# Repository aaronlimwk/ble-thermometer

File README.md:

# BLE Contactless Thermometer 🤒
A BLE contactless thermometer which can distinguish between colds and the flu!

## Front & Back View 🌡️

## Features ⚙️

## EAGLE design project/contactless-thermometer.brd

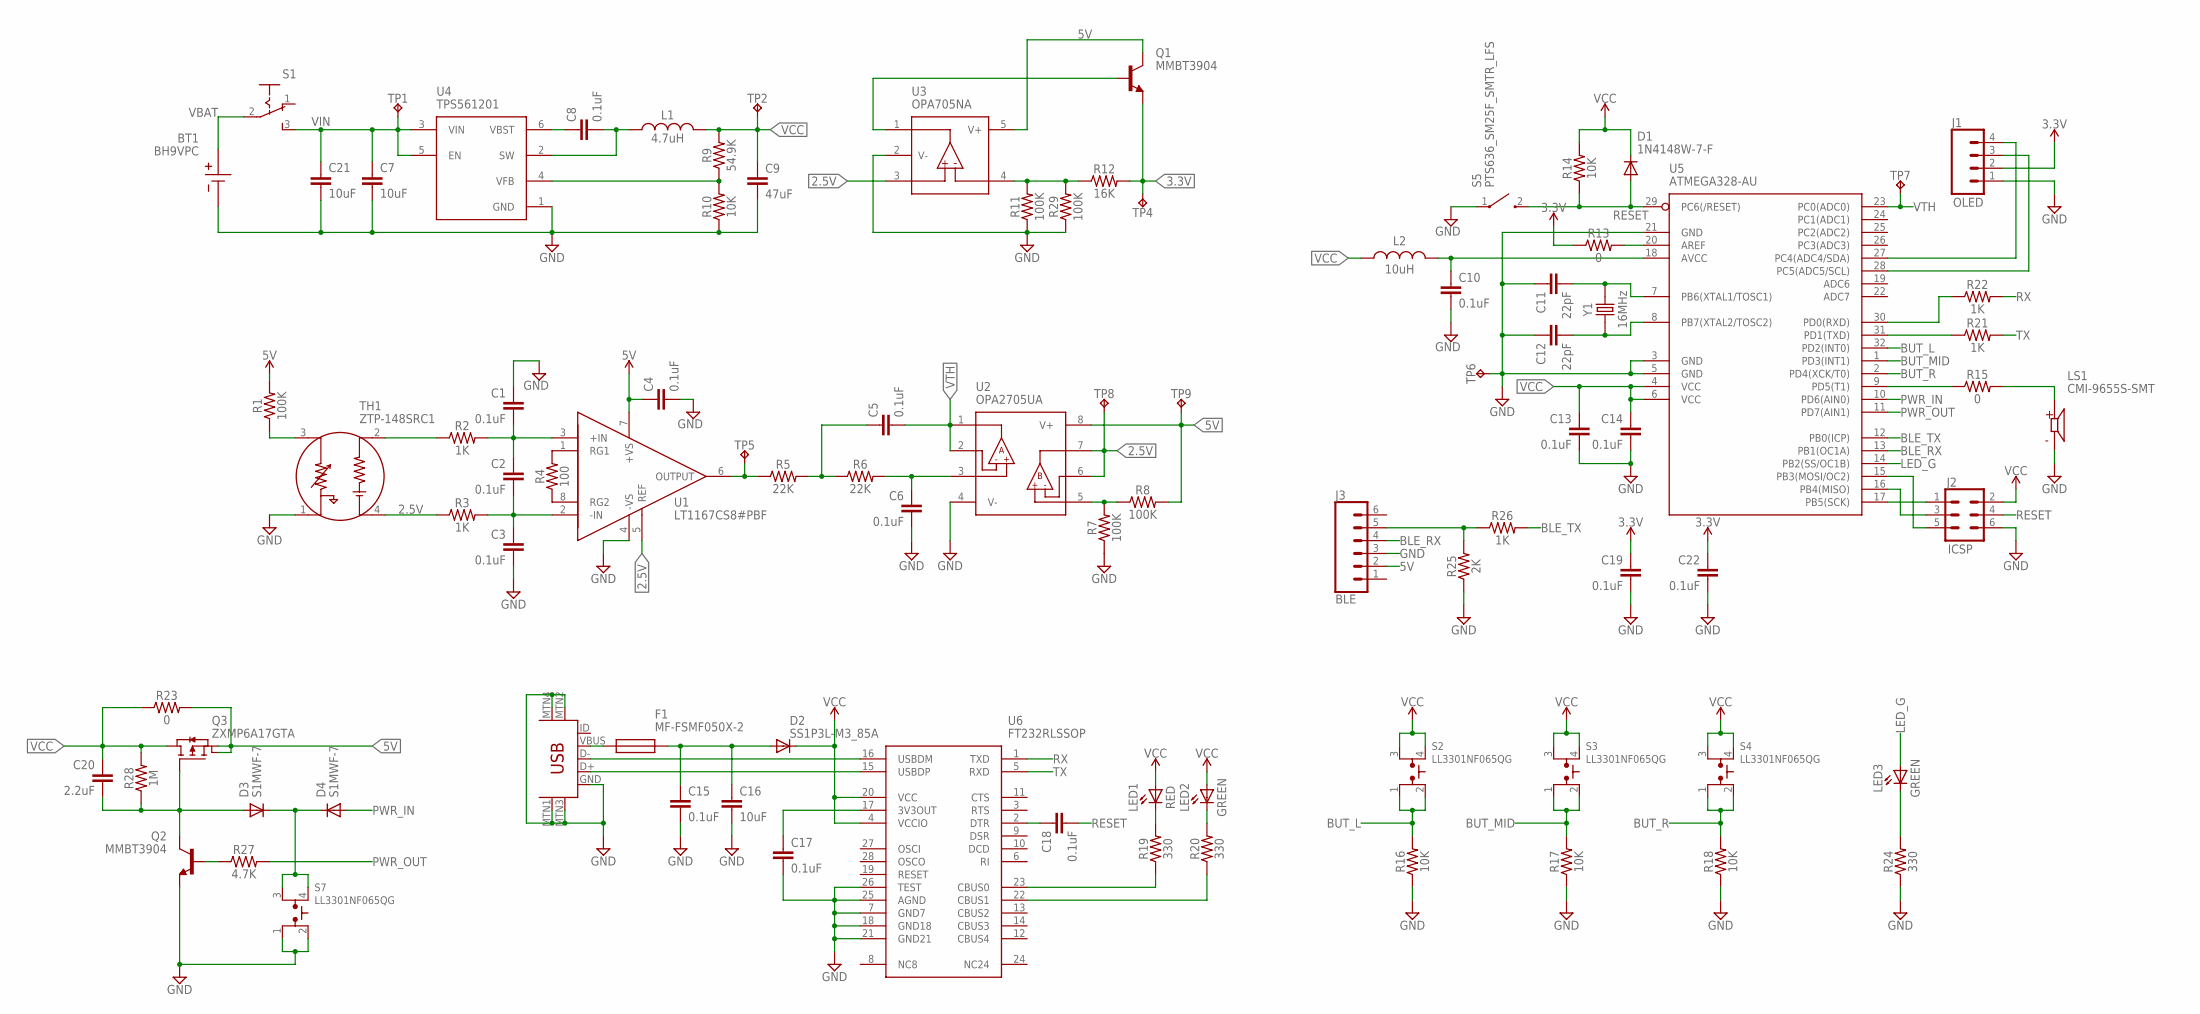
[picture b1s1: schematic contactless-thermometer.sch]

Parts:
BT1: BH9VPC; BAT_BH9VPC
C1, C2, C3, C4, C5, C6, C8, C10, C13, C14, C15, C17, C18, C19, C22: 0.1uF; 0603
C7, C21: 10uF; CAPC2012X145N
C9: 47uF; 1206
C11, C12: 22pF; 0603
C16: 10uF; 1206
C20: 2.2uF; CAPC2012X145N
D1: 1N4148W-7-F; SOD3716X145N
D2: SS1P3L-M3_85A; SMP
D3, D4: S1MWF-7; SODFL3518X115N
F1: MF-FSMF050X-2; FUSC1608X100N
J1: OLED; 1X04
J2: ICSP; 2X3
J3: BLE; 1X06
J4: USB-MINIB-5PIN; USB-MINIB
L1: 4.7uH; VLCF5020T4R7N1R71
L2: 10uH; INDC2012X145N
LED1: RED; AA1608CGSK
LED2, LED3: GREEN; AA1608CGSK
LS1: CMI-9655S-SMT; CUI_CMI-9655S-SMT
Q1, Q2: MMBT3904; SOT23_NXP
Q3: ZXMP6A17GTA; SOT230P700X180-4N
R1, R7, R8, R11, R29: 100K; 0603
R2, R3, R21, R22, R26: 1K; 0603
R4: 100; 0603
R5, R6: 22K; 0603
R9: 54.9K; 0603
R10, R14, R16, R17, R18: 10K; 0603
R12: 16K; 0603
R13, R15, R23: 0; 0603
R19, R20, R24: 330; 0603
R25: 2K; 0603
R27: 4.7K; 0603
R28: 1M; 0603
S1: SK12F17G7; SW3_2F17G7_CNK
S2, S3, S4, S7: LL3301NF065QG
S5: PTS636_SM25F_SMTR_LFS; PTS636SM25FSMTRLFS
TH1: ZTP-148SRC1; XDCR_ZTP-148SRC1
TP1, TP2, TP4, TP5, TP6, TP7, TP8, TP9: TPTP10R; TP10R
U1: LT1167CS8#PBF; SOIC127P599X175-8N
U2: OPA2705UA; SOIC127P600X175-8N
U3: OPA705NA; SOT95P280X145-5N
U4: TPS561201; SOT95P280X110-6N
U5: ATMEGA328-AU; TQFP32-08
U6: FT232RLSSOP; SOP65P780X200-28N
Y1: 16MHz; XTAL_ECS-240-20-5PX-TR

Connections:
2.5V: R3.1, TH1.4 (THERMOPILE_GND), TP8.TP, U1.5 (REF), U2.6 (-INB), U2.7 (OUTB), U3.3 (+IN)
3.3V: C19.1, C22.1, J1.2, Q1.2, R12.2, R13.1, TP4.TP
5V: C4.1, J3.2, Q1.3, Q3.2 (D1), Q3.4 (D2), R1.2, R8.2, R23.2, TP9.TP, U1.7 (+VS), U2.8 (V+), U3.5 (V+)
AVCC: C10.1, L2.2, U5.18 (AVCC)
BLE_TX: R26.2, U5.12 (PB0(ICP))
BUT_L: R16.2, S2.1, S2.2, U5.32 (PD2(INT0))
BUT_MID: R17.2, S3.1, S3.2, U5.1 (PD3(INT1))
BUT_R: R18.2, S4.1, S4.2, U5.2 (PD4(XCK/T0))
BUZZ: R15.1, U5.9 (PD5(T1))
DTR: C18.1, U6.2 (DTR)
GND: BT1.-, C1.1, C3.2, C4.2, C6.2, C7.1, C9.2, C10.2, C11.1, C12.1, C13.2, C14.2, C15.2, C16.2, C17.2, C19.2, C21.1, C22.2, J1.1, J2.6, J3.3, J4.GND, J4.MTN1 (MTN2), J4.MTN2 (MTN3), J4.MTN3 (MTN1), J4.MTN4, LS1.N, Q2.2, R7.1, R10.1, R11.1, R16.1, R17.1, R18.1, R24.1, R25.1, R29.1, S5.1 (COM), S7.1, S7.2, TH1.1 (THERMISTOR_GND), TP6.TP, U1.4 (-VS), U2.4 (V-), U3.2 (V-), U4.1 (GND), U5.3 (GND), U5.5 (GND), U5.21 (GND), U6.7 (GND7), U6.18 (GND18), U6.21 (GND21), U6.25 (AGND), U6.26 (TEST); also elsewhere on the board
LED_G: LED3.2 (A), U5.14 (PB2(SS/OC1B))
unnamed: C1.2, C2.1, R2.2, U1.3 (+IN)
unnamed: R4.2, U1.1 (RG1)
unnamed: R2.1, TH1.2 (THERMOPILE)
unnamed: C2.2, C3.1, R3.2, U1.2 (-IN)
unnamed: R7.2, R8.1, U2.5 (+INB)
unnamed: R4.1, U1.8 (RG2)
unnamed: R5.1, TP5.TP, U1.6 (OUTPUT)
unnamed: LS1.P, R15.2
unnamed: C5.1, R5.2, R6.1
unnamed: C6.1, R6.2, U2.3 (+INA)
unnamed: R13.2, U5.20 (AREF)
unnamed: J4.D-, U6.16 (USBDM)
unnamed: J4.D+, U6.15 (USBDP)
unnamed: J2.1, U5.17 (PB5(SCK))
unnamed: C8.1, U4.6 (VBST)
unnamed: C11.2, U5.7 (PB6(XTAL1/TOSC1)), Y1.2
unnamed: C12.2, U5.8 (PB7(XTAL2/TOSC2)), Y1.1
unnamed: J2.3, U5.16 (PB4(MISO))
unnamed: C8.2, L1.1, U4.2 (SW)
unnamed: J2.5, U5.15 (PB3(MOSI/OC2))
unnamed: R9.1, R10.2, U4.4 (VFB)
unnamed: R11.2, R12.1, R29.2, U3.4 (-IN)
unnamed: R19.1, U6.23 (CBUS0)
unnamed: J1.4, U5.27 (PC4(ADC4/SDA))
unnamed: LED1.1 (K), R19.2
unnamed: R20.1, U6.22 (CBUS1)
unnamed: J1.3, U5.28 (PC5(ADC5/SCL))
unnamed: LED2.1 (K), R20.2
unnamed: C17.1, U6.17 (3V3OUT)
unnamed: F1.1, J4.VBUS
unnamed: Q1.1, U3.1 (OUT)
unnamed: C15.1, C16.1, D2.1 (A), F1.2
unnamed: R21.1, U5.31 (PD1(TXD))
unnamed: R22.1, U5.30 (PD0(RXD))
unnamed: Q2.1, R27.1
unnamed: LED3.1 (K), R24.2
unnamed: J3.5, R25.2, R26.1
unnamed: C20.1, D3.2 (A), Q2.3, Q3.1 (G), R28.1
unnamed: D3.1 (K), D4.1 (K), S7.3, S7.4
PWR_IN: D4.2 (A), U5.10 (PD6(AIN0))
PWR_OUT: R27.2, U5.11 (PD7(AIN1))
RESET: C18.2, D1.2 (A), J2.4, R14.1, S5.2 (NO), U5.29 (PC6(/RESET))
RX: R22.2, U6.1 (TXD)
TX: R21.2, U6.5 (RXD)
VBAT: BT1.+, S1.2
VCC: C9.1, C13.1, C14.1, C20.2, D1.1 (K), D2.2 (K), J2.2, L1.2, L2.1, LED1.2 (A), LED2.2 (A), Q3.3 (S), R9.2, R14.2, R23.1, R28.2, S2.3, S2.4, S3.3, S3.4, S4.3, S4.4, TP2.TP, U5.4 (VCC), U5.6 (VCC), U6.4 (VCCIO), U6.20 (VCC)
VIN: C7.2, C21.2, S1.3, TP1.TP, U4.3 (VIN), U4.5 (EN)
VR: R1.1, TH1.3 (THERMISTOR), U5.24 (PC1(ADC1))
VTH: C5.2, TP7.TP, U2.1 (OUTA), U2.2 (-INA), U5.23 (PC0(ADC0))

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
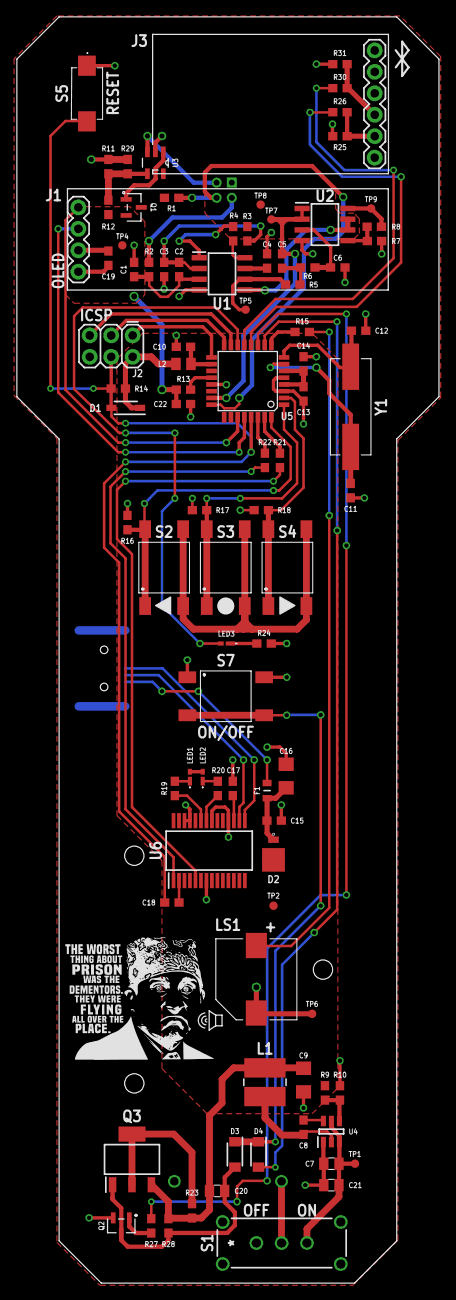
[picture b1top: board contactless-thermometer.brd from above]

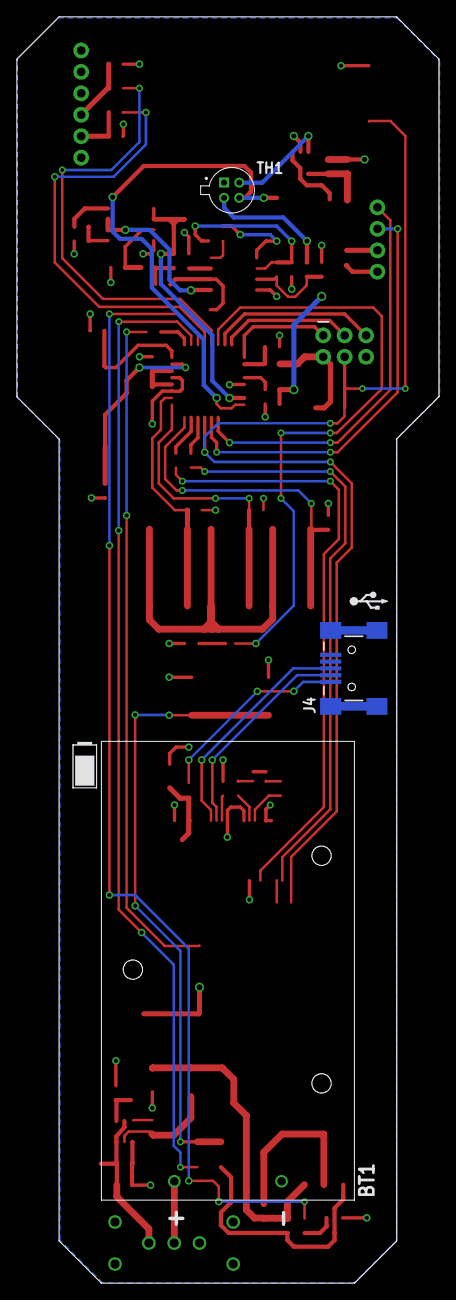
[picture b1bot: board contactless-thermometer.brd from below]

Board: 2 copper layers, 50.0 x 150.0 mm, 94 parts (3 on the bottom side), 63 nets.

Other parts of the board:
R30: 1K; 0603
R31: 2K; 0603

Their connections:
GND: R31.1; also elsewhere on the board

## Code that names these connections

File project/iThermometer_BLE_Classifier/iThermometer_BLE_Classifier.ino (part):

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#define baud 9600

// Pin Definitions
#define BUT_L     2
#define BUT_MID   3
#define BUT_R     4
#define BUZZ      5
#define PWR_IN    6
#define PWR_OUT   7
#define LED       10
#define VTH       14
#define BLE_STATE 16


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  analogReference(EXTERNAL);
  // Pin Setup
  pinMode(BLE_STATE, INPUT);
  pinMode(VTH,INPUT);
  pinMode(PWR_OUT, OUTPUT);
  pinMode(LED, OUTPUT);
  pinMode(BUZZ, OUTPUT);
  //Turn off LED
  digitalWrite(LED, LOW);

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
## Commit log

2021-04-27 add schematic and layout
2021-04-27 add switch
2021-04-27 Placement
2021-04-27 settle conflicts
2021-04-27 alignment fix
2021-04-27 alignment issue
2021-04-28 PCB progress
2021-04-28 allah
2021-04-29 update silkscreen
2021-04-29 Update 3
2021-04-29 fixed silkscreen
2021-04-30 update silkscreen and schematic
2021-04-30 snake
2021-04-30 Major Updates
2021-04-30 update major
2021-04-30 major update 2
2021-04-30 big bosses big
2021-04-30 big bouses big
2021-04-30 just wonderful
2021-04-30 biiiiitch
2021-05-06 update schematics
2021-05-19 arduino menu sketch
2021-05-24 Bluetooth Updates
2021-05-27 too good bro
2021-05-27 added classifier
2021-05-28 yeaaaa
2021-05-29 Firmware update 10
2021-05-30 Saturday updates yo
    gotta get more lines
2021-05-30 Firmware_Version1
2021-05-31 name
2021-05-31 final version
2022-01-13 adding slides

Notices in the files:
parts and their libraries:
SparkFun: Licensing: CC v3.0 Share-Alike You are welcome to use this library for commercial purposes.
SparkFun-Connectors: Licensing: Creative Commons ShareAlike 4.0 International - https://creativecommons.org/licenses/by-sa/4.0
COPYRIGHT: Copyright (C) 2018 Accelerated Designs. All rights reserved
